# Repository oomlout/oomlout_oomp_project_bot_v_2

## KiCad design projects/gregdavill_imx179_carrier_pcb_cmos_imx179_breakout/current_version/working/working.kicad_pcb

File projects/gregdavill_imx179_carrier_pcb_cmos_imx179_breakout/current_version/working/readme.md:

# imx179_carrier_pcb
 
## summary 
* id: gregdavill_imx179_carrier_pcb_cmos_imx179_breakout
* user: gregdavill
* name: imx179_carrier_pcb
* board: cmos_imx179_breakout
* repo: https://github.com/gregdavill/imx179-carrier-pcb
* src_file_repo_kicad_pcb: hardware/cmos-imx179/cmos-imx179-breakout.kicad_pcb
* src_file_repo_kicad_pcb_link: https://github.com/gregdavill/imx179-carrier-pcb/tree/master/hardware/cmos-imx179/cmos-imx179-breakout.kicad_pcb

* src_file_repo_sch: hardware/cmos-imx179/cmos-imx179-breakout.sch
* src_file_repo_sch_link: https://github.com/gregdavill/imx179-carrier-pcb/tree/master/hardware/cmos-imx179/cmos-imx179-breakout.sch
* full details link: https://github.com/oomlout/oomlout_oomp_project_bot_v_2/tree/main/projects/gregdavill_imx179_carrier_pcb_cmos_imx179_breakout/current_version/working

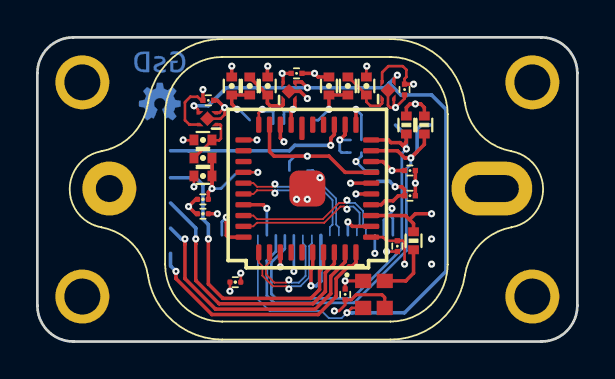
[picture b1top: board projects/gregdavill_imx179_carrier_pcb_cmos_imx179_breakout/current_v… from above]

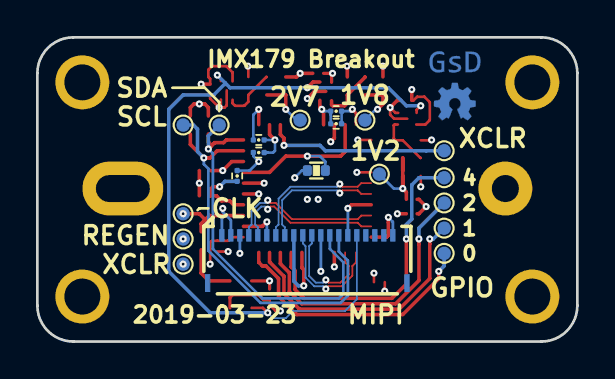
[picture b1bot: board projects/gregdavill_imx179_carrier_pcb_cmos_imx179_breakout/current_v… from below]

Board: 4 copper layers, 30.0 x 16.9 mm, 34 parts (7 on the bottom side), 20 nets.

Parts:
C1, C3, C5, C9, C10, C11: 1uF; C_0402
C7, C12, C13, C14, C15, C16, C17, C18, C19, C20, C21, C22, C23, C24, C25: 100nF; C_0201
J1: Conn_01x20; 5034802000
L1, L2, L3: 600R; C_0402
R1, R2: 2.2K; R_0402
R3: 22R; R_0402
R4: 0R; R_0402
U1: NCP114-120; X2SON_4_1.0x1.0mm
U2: NCP167-180; X2SON_4_1.0x1.0mm
U3: imx179-plcc40; PLCC-40_sony
U4: NCP167-270; X2SON_4_1.0x1.0mm
U5: 24.00 MHz; CDFN3225-4LD-PL-1

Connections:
+1V2: C5.1, C7.1, C18.1, C22.1, C23.1, C24.1, C25.1, L1.1, U3.5, U3.26, U3.37
+1V8: C10.1, C12.1, C13.1, C19.1, C20.1, C21.1, L2.1, R1.1, R2.1, U3.29, U5.1
+2V7: C11.1, C14.1, L3.1, U3.3, U3.33
+3V3: C15.1, C16.1, C17.1, J1.1, J1.2, U1.4, U2.4, U4.4
/AGND: R4.1, U3.4, U3.32
/CAM_SCL: J1.14, R1.2, U3.34
/CAM_SDA: J1.13, R2.2, U3.35
/CLK_IN: R3.2, U3.28
/CLK_N: J1.5, U3.14
/CLK_P: J1.4, U3.13
/DATA0_N: J1.8, U3.11
/DATA0_P: J1.7, U3.10
/DATA1_N: J1.11, U3.17
/DATA1_P: J1.10, U3.16
/ENABLE: J1.16, U1.3, U2.3, U4.3, U5.2
GND: C1.2, C3.2, C5.2, C7.2, C9.2, C10.2, C11.2, C12.2, C13.2, C14.2, C15.2, C16.2, C17.2, C18.2, C19.2, C20.2, C21.2, C22.2, C23.2, C24.2, C25.2, J1.3, J1.6, J1.9, J1.12, J1.15, J1.20, R4.2, U1.2, U2.2, U3.2, U3.6, U3.9, U3.12, U3.15, U3.18, U3.21, U3.27, U3.36, U3.41, U4.2, U5.3
unnamed: C1.1, L2.2, U2.1
unnamed: C3.1, L1.2, U1.1
unnamed: C9.1, L3.2, U4.1
unnamed: R3.1, U5.4

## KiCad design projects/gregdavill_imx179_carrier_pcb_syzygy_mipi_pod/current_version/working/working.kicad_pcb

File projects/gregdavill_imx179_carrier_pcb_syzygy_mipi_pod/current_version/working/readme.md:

# imx179_carrier_pcb
 
## summary 
* id: gregdavill_imx179_carrier_pcb_syzygy_mipi_pod
* user: gregdavill
* name: imx179_carrier_pcb
* board: syzygy_mipi_pod
* repo: https://github.com/gregdavill/imx179-carrier-pcb
* src_file_repo_kicad_pcb: hardware/syzygy-mipi-pod/syzygy-mipi-pod.kicad_pcb
* src_file_repo_kicad_pcb_link: https://github.com/gregdavill/imx179-carrier-pcb/tree/master/hardware/syzygy-mipi-pod/syzygy-mipi-pod.kicad_pcb

* src_file_repo_sch: hardware/cmos-imx179/cmos-imx179-breakout.sch
* src_file_repo_sch_link: https://github.com/gregdavill/imx179-carrier-pcb/tree/master/hardware/cmos-imx179/cmos-imx179-breakout.sch
* full details link: https://github.com/oomlout/oomlout_oomp_project_bot_v_2/tree/main/projects/gregdavill_imx179_carrier_pcb_syzygy_mipi_pod/current_version/working

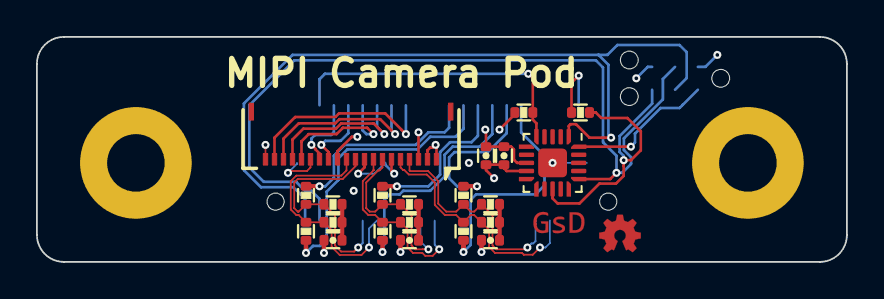
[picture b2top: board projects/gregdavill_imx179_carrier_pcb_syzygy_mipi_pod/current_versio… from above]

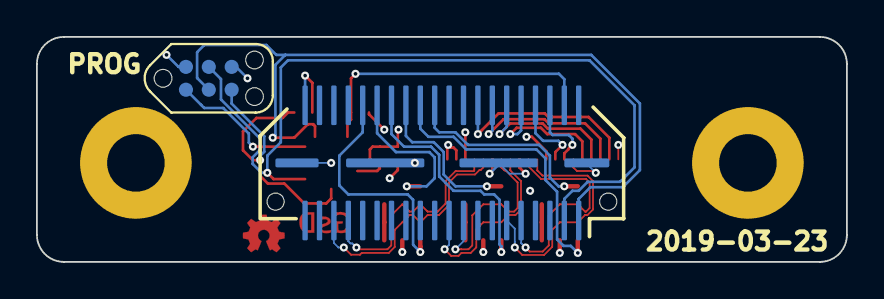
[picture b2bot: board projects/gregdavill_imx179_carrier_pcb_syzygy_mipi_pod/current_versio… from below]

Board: 4 copper layers, 45.0 x 12.5 mm, 23 parts (2 on the bottom side), 28 nets.

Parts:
C1, C2, C3: 100pF; C_0402
C14: 100nF; C_0402
C15: 1uF; C_0402
J1: SYZYGY-STD; SYZYGY_standard_pod
J2: Conn_01x20; 5034802000
J3: TagConnect; TC2030-NL_SMALL
R1, R14: 10K; R_0402
R2, R3, R4, R5, R6, R7: 150R; R_0402
R8, R9, R10, R11, R12, R13: 100R; R_0402
U1: ATtiny44A-MMH; QFN-20-1EP_3x3mm_P0.45mm_EP1.6x1.6mm

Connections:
+3V3: C14.1, C15.1, J1.40, J2.1, J2.2, J3.2, R1.1, R14.1, U1.9
/CAM0_CLK_N: J1.35, J2.5, R3.1, R9.2
/CAM0_CLK_P: J1.33, J2.4, R2.2, R8.2
/CAM0_D0_N: J1.19, J2.8, R5.1, R11.2
/CAM0_D0_P: J1.17, J2.7, R4.2, R10.2
/CAM0_D1_N: J1.11, J2.11, R7.1, R13.2
/CAM0_D1_P: J1.9, J2.10, R6.2, R12.2
/CAM0_SCL: J1.6, J2.14
/CAM0_SDA: J1.8, J2.13
/GPIO0: J1.10, J2.16
/GPIO1: J1.12, J2.17
/GPIO2: J1.14, J2.18
/GPIO3: J1.16, J2.19
/Peripheral MCU/MISO: J3.1, U1.20
/Peripheral MCU/~RESET: J3.5, R14.2, U1.13
/RGA: J1.4, R1.2, U1.5
/SCL: J1.1, J3.3, U1.1
/SDA: J1.3, J3.4, U1.16
/TERM_0_N: J1.28, R11.1
/TERM_0_P: J1.26, R10.1
/TERM_1_N: J1.24, R13.1
/TERM_1_P: J1.22, R12.1
/TERM_CLK_N: J1.32, R9.1
/TERM_CLK_P: J1.30, R8.1
GND: C1.2, C2.2, C3.2, C14.2, C15.2, J1.41, J2.3, J2.6, J2.9, J2.12, J2.15, J2.20, J3.6, U1.8, U1.21
unnamed: C1.1, R2.1, R3.2
unnamed: C2.1, R4.1, R5.2
unnamed: C3.1, R6.1, R7.2

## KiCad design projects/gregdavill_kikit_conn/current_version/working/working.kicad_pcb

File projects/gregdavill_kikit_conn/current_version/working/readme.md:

# kikit
 
## summary 
* id: gregdavill_kikit_conn
* user: gregdavill
* name: kikit
* board: conn
* repo: https://github.com/gregdavill/KiKit
* src_file_repo_kicad_pcb: test/resources/conn-fail.kicad_pcb
* src_file_repo_kicad_pcb_link: https://github.com/gregdavill/KiKit/tree/master/test/resources/conn-fail.kicad_pcb

* src_file_repo_sch: 
* src_file_repo_sch_link: https://github.com/gregdavill/KiKit/tree/master/
* full details link: https://github.com/oomlout/oomlout_oomp_project_bot_v_2/tree/main/projects/gregdavill_kikit_conn/current_version/working

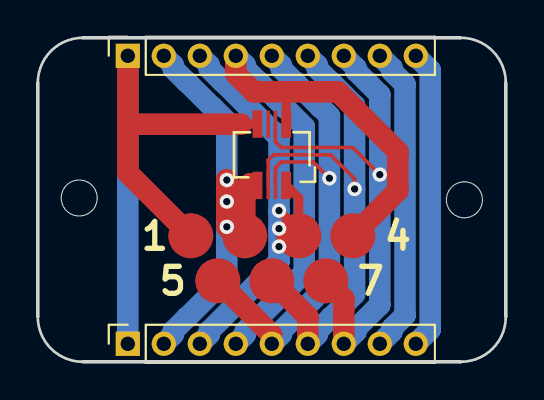
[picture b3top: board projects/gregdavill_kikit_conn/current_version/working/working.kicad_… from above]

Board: 2 copper layers, 26.0 x 18.0 mm, 6 parts (0 on the bottom side), 9 nets.

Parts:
H1, H2: MountingHole; MountingHole_2mm
J1: IN; PinSocket_1x09_P2.00mm_Vertical
J2: OUT; PinSocket_1x09_P2.00mm_Vertical
J3: POGO; pogo_pads_4_3
J4: Molex; molex-505004-0812

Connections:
1: J1.1, J2.1, J3.1, J4.8
2: J1.2, J2.2, J3.2, J4.7
3: J1.3, J2.3, J3.3, J4.1
4: J1.4, J2.4, J3.4, J4.2
5: J1.5, J2.5, J3.5, J4.3
6: J1.6, J2.6, J3.6, J4.5
7: J1.7, J2.7, J3.7, J4.4
8: J1.8, J2.8
9: J1.9, J2.9

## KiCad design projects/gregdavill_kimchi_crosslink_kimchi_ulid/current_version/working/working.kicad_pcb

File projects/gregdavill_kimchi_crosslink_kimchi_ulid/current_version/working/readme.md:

# kimchi_crosslink
 
## summary 
* id: gregdavill_kimchi_crosslink_kimchi_ulid
* user: gregdavill
* name: kimchi_crosslink
* board: kimchi_ulid
* repo: https://github.com/gregdavill/kimchi-crosslink
* src_file_repo_kicad_pcb: kimchi_ulid.kicad_pcb
* src_file_repo_kicad_pcb_link: https://github.com/gregdavill/kimchi-crosslink/tree/main/kimchi_ulid.kicad_pcb
* src_file_repo_kicad_sch: kimchi_ulid.kicad_sch
* src_file_repo_kicad_sch_link: https://github.com/gregdavill/kimchi-crosslink/tree/main/kimchi_ulid.kicad_sch

* src_file_repo_sch: kimchi_ulid.sch
* src_file_repo_sch_link: https://github.com/gregdavill/kimchi-crosslink/tree/main/kimchi_ulid.sch
* full details link: https://github.com/oomlout/oomlout_oomp_project_bot_v_2/tree/main/projects/gregdavill_kimchi_crosslink_kimchi_ulid/current_version/working

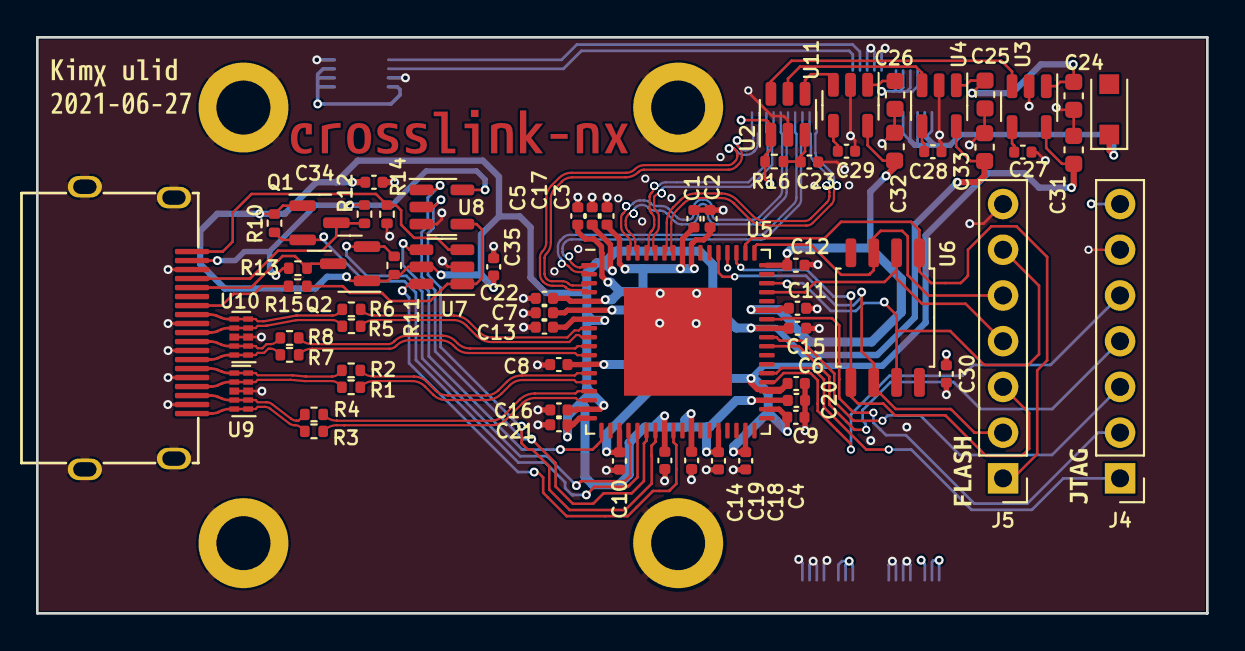
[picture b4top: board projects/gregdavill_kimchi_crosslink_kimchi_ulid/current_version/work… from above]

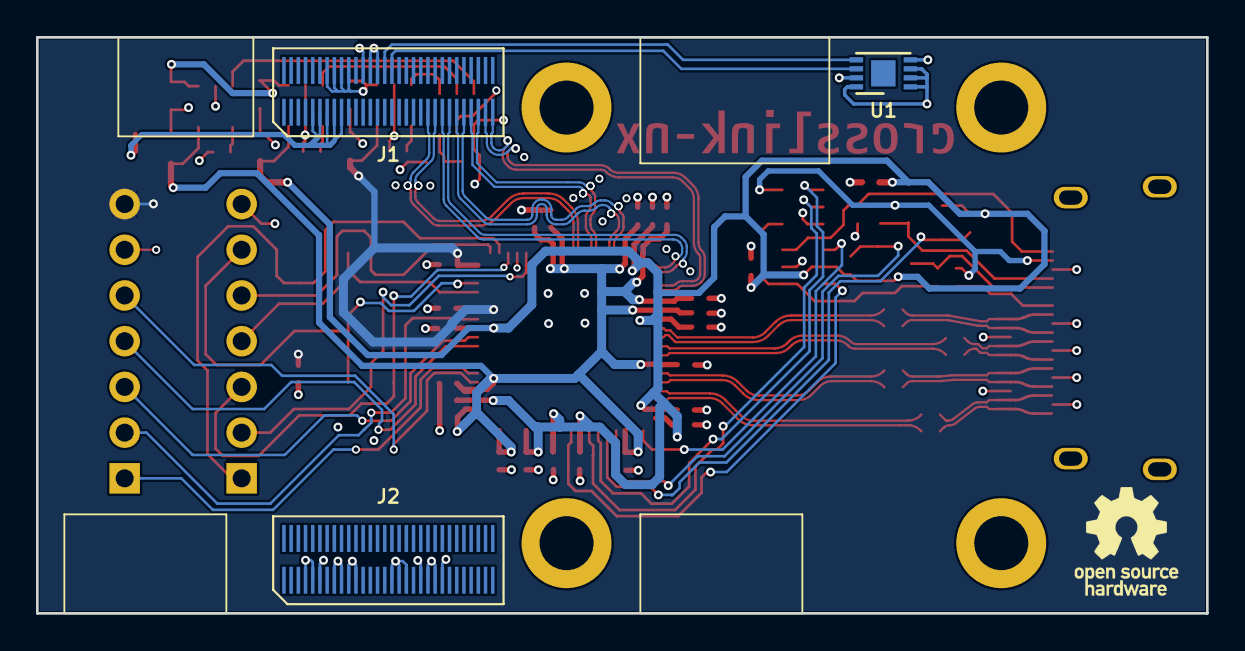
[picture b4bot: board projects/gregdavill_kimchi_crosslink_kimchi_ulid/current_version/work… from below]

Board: 4 copper layers, 65.0 x 32.0 mm, 80 parts (9 on the bottom side), 66 nets.

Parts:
C1, C2, C3, C4, C5, C6, C7, C8, C9, C10, C11, C12, C13, C14, C15, C16, C17, C18, C19, C20, C21, C22, C30, C34, C35: 0.1uF; C_0402_1005Metric
C23: C; C_0402_1005Metric
C24, C25, C26: 4.7uF; C_0603_1608Metric
C27, C28, C29: 0.01uF; C_0402_1005Metric
C31, C32, C33: 10uF; C_0603_1608Metric
D1: PMEG1020EH; D_SOD-123F
H1, H2, H3, H4: MountingHole_Pad; MountingHole_M2_Standoff
J1, J2: DF40HC(3.5)-60DS
J3: HDMI_A_1.4; HDMI-10029449-111RLF
J4: Jtag; PinHeader_1x07_P2.54mm_Vertical
J5: Flash; PinHeader_1x07_P2.54mm_Vertical
K1: KIMCHI_MICRO
LOGO1: Logo_Open_Hardware_Small; OSHW-Logo_5.7x6mm_SilkScreen
Q1, Q2: 2N7002; SOT-23
R1, R2, R3, R4, R5, R6, R7, R8, R16: R; R_0402_1005Metric
R10, R11, R12, R13: 2k2; R_0402_1005Metric
R14: 47k; R_0402_1005Metric
R15: 100R; R_0402_1005Metric
U1: 24C32; DFN-8-1EP_3x2mm_P0.5mm_EP1.36x1.46mm
U2: LM3880; SOT-23-6
U3, U4, U11: LD3985M27R_SOT23; SOT-23-5
U5: LIFCL40-NX; QFN-72-1EP_10x10mm_P0.5mm_EP6x6mm
U6: W25Q32JVSS; SOIC-8_5.23x5.23mm_P1.27mm
U7: 74LVC2G17; SOT-23-6
U8: 74LVC1G125; SOT-23-5
U9, U10: TPD4E02B04DQA; USON-10_2.5x1.0mm_P0.5mm
svg2mod, svg2mod#2, svg2mod#3, svg2mod#4, svg2mod#5: G***; svg2mod

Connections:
+1V0: C1.1, C2.1, C3.1, C4.1, C5.1, C6.1, C7.1, C8.1, C9.1, C10.1, C22.1, C31.1, U3.5 (VOUT), U5.5 (VCC), U5.6 (VCC), U5.12 (VCCPLL_LLC), U5.21 (VCC), U5.35 (VCC), U5.38 (VCCPLL_LRC), U5.40 (VCC), U5.62 (VCC), U5.63 (VCCPLLDPHY0), U5.70 (VCCDPHY0), U5.72 (VCCDPHY0)
+1V8: C13.1, C14.1, C15.1, C16.1, C17.1, C18.1, C19.1, C20.1, C21.1, C33.1, C34.1, C35.1, Q1.1 (G), Q2.1 (G), R10.2, R11.2, U4.5 (VOUT), U5.7 (VCCAUX), U5.17 (VCCAUXH5), U5.18 (VCCIO5), U5.26 (VCCIO3), U5.29 (VCCAUXH3), U5.32 (VCCIO3), U5.39 (VCCADC18), U5.47 (VCCAUX), U5.71 (VCCADPHY0), U7.5 (VCC)
+3V3: C11.1, C12.1, C30.1, C32.1, J4.7, U5.49 (VCCIO1), U5.54 (VCCIO0), U11.5 (VOUT)
/DISP_CK_N: J1.35, U5.69 (DPHY0_CKN)
/DISP_CK_P: J1.36, U5.68 (DPHY0_CKP)
/DISP_D0_N: J1.31, U5.3 (DPHY0_DN0)
/DISP_D0_P: J1.32, U5.4 (DPHY0_DP0)
/DISP_D1_N: J1.33, U5.67 (DPHY0_DN1)
/DISP_D1_P: J1.34, U5.66 (DPHY0_DP1)
/DISP_D2_N: J1.37, U5.2 (DPHY0_DN2)
/DISP_D2_P: J1.38, U5.1 (DPHY0_DP2)
/DISP_D3_N: J1.39, U5.65 (DPHY0_DN3)
/DISP_D3_P: J1.40, U5.64 (DPHY0_DP3)
/FLASH_CS: J5.1, U5.56 (PT78A/MCSN/PCLKT0_1), U6.1 (~CS)
/FLASH_MISO|IO1: J5.4, U5.51 (PT80A/MISO/MD1), U6.2 (DO(IO1))
/FLASH_MOSI|IO0: J5.3, U5.57 (PT78B/MOSI/MD0), U6.5 (DI(IO0))
/FLASH_~HLD|~RST|IO3: J5.6, U5.52 (PT82A/MD3), U6.7 (IO3)
/FLASH_~WP|IO2: J5.5, U5.55 (PT80B/MD2), U6.3 (IO2)
/IO: J4.1, U5.42 (PR11A/SDA/USER_SDA)
/TCK: J4.5, U5.41 (PR13A/TCK/SCLK/PMU_EXT_CLK)
/TDI: J4.3, U5.46 (PR8B/TDI/SSI)
/TDO: J4.4, U5.45 (PR10B/TDO/SSO)
/TMS: J4.2, U5.48 (PR6B/TMS/SCSN)
/_tmds_clk+: J3.10 (CK+), R5.2, U10.4 (IO3)
/_tmds_clk-: J3.12 (CK-), R6.2, U10.5 (IO4)
/_tmds_d0+: J3.7 (D0+), R7.2, U10.1 (IO1)
/_tmds_d0-: J3.9 (D0-), R8.2, U10.2 (IO2)
/_tmds_d1+: J3.4 (D1+), R1.2, U9.4 (IO3)
/_tmds_d1-: J3.6 (D1-), R2.2, U9.5 (IO4)
/_tmds_d2+: J3.1 (D2+), R3.2, U9.1 (IO1)
/_tmds_d2-: J3.3 (D2-), R4.2, U9.2 (IO2)
/en0: U2.6 (FLAG1), U3.3 (INH)
/en1: U2.5 (FLAG2), U4.3 (INH)
/en2: U2.4 (FLAG3), U11.3 (INH)
/iCE_SCK: J5.2, U5.59 (PT76A/MCLK/PCLKT0_0), U6.6 (CLK)
/tmds_clk+: R5.1, U5.9 (PB12A/PCLKT5_3)
/tmds_clk-: R6.1, U5.8 (PB12B/PCLKC5_3/VREF5_2)
/tmds_d0+: R7.1, U5.11 (PB8A/PCLKT5_1/LLC_GPLL0T_IN/ADC_CP3)
/tmds_d0-: R8.1, U5.10 (PB8B/PCLKC5_1/LLC_GPLL0C_IN/ADC_CN3)
/tmds_d1+: R1.1, U5.14 (PB4A/CDR_RXP0/VREF5_1/ADC_CP0/COMP1P)
/tmds_d1-: R2.1, U5.13 (PB4B/CDR_RXN0/ADC_CN0/COMP1N)
/tmds_d2+: R3.1, U5.16 (PB6A/PCLKT5_0/CDR_RXP1/ADC_CP1/COMP2P)
/tmds_d2-: R4.1, U5.15 (PB6B/PCLKC5_0/CDR_RXN1/ADC_CN1/COMP2N)
GND: C1.2, C2.2, C3.2, C4.2, C5.2, C6.2, C7.2, C8.2, C9.2, C10.2, C11.2, C12.2, C13.2, C14.2, C15.2, C16.2, C17.2, C18.2, C19.2, C20.2, C21.2, C22.2, C23.2, C24.2, C25.2, C26.2, C27.2, C28.2, C29.2, C30.2, C31.2, C32.2, C33.2, C34.2, C35.2, H1.1, H2.1, H3.1, H4.1, J1.12, J1.13, J1.14, J2.38, J2.39, J2.40, J2.41, J2.50, J2.51, J2.52, J2.53, J3.2 (D2S), J3.5 (D1S), J3.8 (D0S), J3.11 (CKS), J3.17 (GND), J3.SH, J4.6, J5.7, R14.1, U1.4 (GND), U1.7 (WP), U2.2 (GND), U3.2 (GND), U4.2 (GND), U5.73 (GND), U7.2 (GND), U8.3 (GND), U9.3 (G), U9.8 (G), U10.3 (G), U10.8 (G), U11.2 (GND)
I2C4_SCL: J1.16, U1.6 (SCL)
I2C4_SDA: J1.15, U1.5 (SDA)
unnamed: C23.1, R16.2, U2.3 (EN)
unnamed: C27.1, U3.4 (BYP)
unnamed: C28.1, U4.4 (BYP)
unnamed: C29.1, U11.4 (BYP)
unnamed: J3.13 (CEC), R15.1
unnamed: J3.15 (SCL), Q2.3 (D), R13.1
unnamed: J3.16 (SDA), Q1.3 (D), R12.1
unnamed: J3.19 (HPD/HEAC-), R14.2, U7.3
unnamed: Q1.2 (S), R10.1, U5.23 (PB54B/PCLKC3_0/ADC_CN5)
unnamed: Q2.2 (S), R11.1, U5.22 (PB54A/PCLKT3_0/VREF3_1/ADC_CP5)
unnamed: R15.2, U7.1, U8.4
unnamed: U5.19 (PB10A/PCLKT5_2/ADC_CP2/COMP3P), U7.4
unnamed: U5.24 (PB58A/PCLKT3_1/ADC_CP6), U8.1
unnamed: U5.25 (PB58B/PCLKC3_1/ADC_CN6), U8.2
unnamed: U5.27 (PB68A/ADC_CP8), U7.6
VCHG: D1.1 (K), J1.52, J1.53, J1.54, J1.55, J1.56
VDD: J3.18 (+5V), R12.2, R13.2, U8.5 (VDD)
VDD_1V8: J2.43, J2.44, J2.45
VDD_3V3: C24.1, C25.1, J2.55, J2.56, J2.57, R16.1, U1.1 (A0), U1.2 (A1), U1.3 (A2), U1.8 (VCC), U2.1 (VCC), U3.1 (VIN), U4.1 (VIN)
VDD_5V: C26.1, J1.7, J1.8, J1.9, J1.10, U11.1 (VIN)

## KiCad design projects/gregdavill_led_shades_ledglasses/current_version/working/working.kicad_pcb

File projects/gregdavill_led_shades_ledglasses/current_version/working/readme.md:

# led_shades
 
## summary 
* id: gregdavill_led_shades_ledglasses
* user: gregdavill
* name: led_shades
* board: ledglasses
* repo: https://github.com/gregdavill/led-shades
* src_file_repo_kicad_pcb: hw/ledGlasses.kicad_pcb
* src_file_repo_kicad_pcb_link: https://github.com/gregdavill/led-shades/tree/master/hw/ledGlasses.kicad_pcb

* src_file_repo_sch: hw/ledGlasses.sch
* src_file_repo_sch_link: https://github.com/gregdavill/led-shades/tree/master/hw/ledGlasses.sch
* full details link: https://github.com/oomlout/oomlout_oomp_project_bot_v_2/tree/main/projects/gregdavill_led_shades_ledglasses/current_version/working

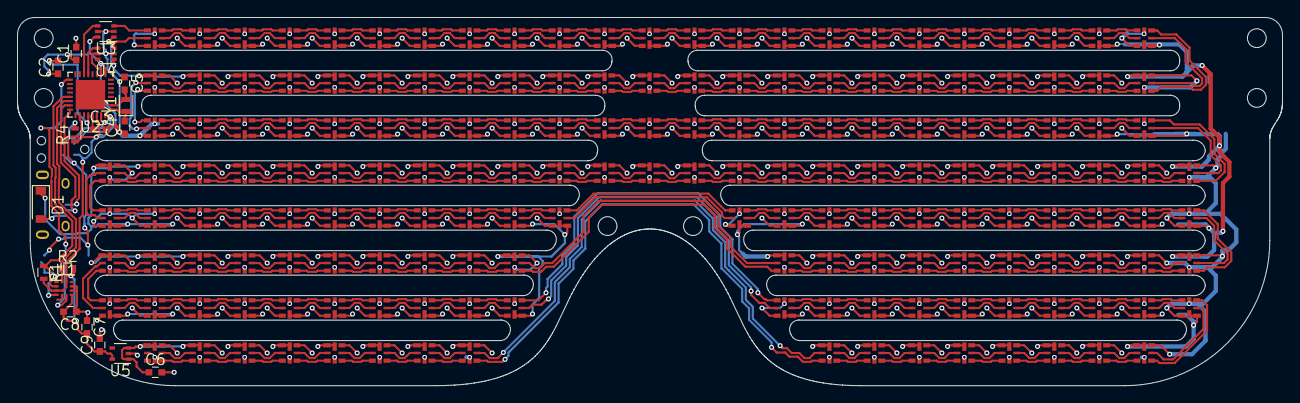
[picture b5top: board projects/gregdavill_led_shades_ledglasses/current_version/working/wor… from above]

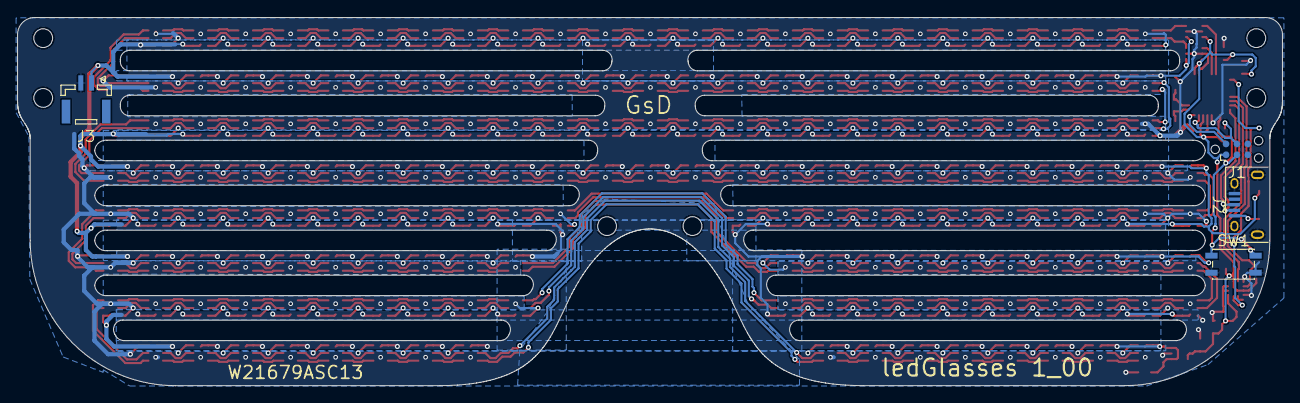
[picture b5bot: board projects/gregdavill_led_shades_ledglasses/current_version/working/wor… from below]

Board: 2 copper layers, 148.1 x 43.1 mm, 201 parts (4 on the bottom side), 361 nets.

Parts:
C1, C2, C7, C8: 100nF; C_0603
C3, C6, C9: 1uF; C_0603
C4, C5: 16pF; C_0603
D1: Diode; D_SOD-123
J1: TC2030-CTX; Tag-Connect_TC2030-IDC-NL
J2: USB_OTG; USB_Micro-B
J3: PWR IN; JST_GH_BM02B-GHS-TBT_02x1.25mm_Straight
LED1, LED2, LED3, LED4, LED5, LED6, LED7, LED8, LED9, LED10, LED11, LED12, LED13, LED14, LED15, LED16, LED17, LED18, LED19, LED20, LED21, LED22, LED23, LED24, LED25, LED26, LED27, LED28, LED29, LED30, LED31, LED32, LED33, LED34, LED35, LED36, LED37, LED38, LED39, LED40, LED41, LED42, LED43, LED44, LED45, LED46, LED47, LED48, LED49, LED50, LED51, LED52, LED53, LED54, LED55, LED56, LED57, LED58, LED59, LED60, LED61, LED62, LED63, LED64, LED65, LED66, LED67, LED68, LED69, LED70, LED71, LED72, LED73, LED74, LED75, LED76, LED77, LED78, LED79, LED80, LED81, LED82, LED83, LED84, LED85, LED86, LED87, LED88, LED89, LED90, LED91, LED92, LED93, LED94, LED95, LED96, LED97, LED98, LED99, LED100, LED101, LED102, LED103, LED104, LED105, LED106, LED107, LED108, LED109, LED110, LED111, LED112, LED113, LED114, LED115, LED116, LED117, LED118, LED119, LED120, LED121, LED122, LED123, LED124, LED125, LED126, LED127, LED128, LED129, LED130, LED131, LED132, LED133, LED134, LED135, LED136, LED137, LED138, LED139, LED140, LED141, LED142, LED143, LED144, LED145, LED146, LED147, LED148, LED149, LED150, LED151, LED152, LED153, LED154, LED155, LED156, LED157, LED158, LED159, LED160, LED161, LED162, LED163, LED164, LED165, LED166, LED167, LED168, LED169, LED170, LED171, LED172: APA102; APA102_2020
MH1, MH2, MH3, MH4, MH5, MH6: MountingHole; MountingHole_2.2mm_M2_DIN965
R1, R2: 4K7; R_0603
R4: 1K; R_0603
SW1: TACT_SWITCH; SW_SPST_EVQP2
U1: BMA255
U2: SAMD20E17A-MU; QFN-32-1EP_5x5mm_Pitch0.5mm
U3, U4: SN74LVC1T45; SOT-363_SC-70-6
U5: MIC5365; SOT-353_SC-70-5
Y1: 32.768kHz; Crystal_SMD_2012-2pin_2.0x1.2mm

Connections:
+3V3: C1.1, C2.1, C7.2, C8.2, C9.1, J1.1, R1.2, R2.2, R4.1, U1.3, U1.7, U1.11, U2.9, U2.30, U3.6, U4.6, U5.5
+5V: C6.1, D1.1, J3.1, LED1.1, LED1.7, LED2.1, LED2.7, LED3.1, LED3.7, LED4.1, LED4.7, LED5.1, LED5.7, LED6.1, LED6.7, LED7.1, LED7.7, LED8.1, LED8.7, LED9.1, LED9.7, LED10.1, LED10.7, LED11.1, LED11.7, LED12.1, LED12.7, LED13.1, LED13.7, LED14.1, LED14.7, LED15.1, LED15.7, LED16.1, LED16.7, LED17.1, LED17.7, LED18.1, LED18.7, LED19.1, LED19.7, LED20.1, LED20.7, LED21.1, LED21.7, LED22.1, LED22.7, LED23.1, LED23.7, LED24.1, LED24.7, LED25.1, LED25.7, LED26.1, LED26.7, LED27.1, LED27.7, LED28.1, LED28.7, LED29.1, LED29.7, LED30.1, LED30.7, LED31.1, LED31.7, LED32.1, LED32.7, LED33.1, LED33.7, LED34.1, LED34.7, LED35.1, LED35.7, LED36.1, LED36.7, LED37.1, LED37.7, LED38.1, LED38.7, LED39.1, LED39.7, LED40.1, LED40.7, LED41.1, LED41.7, LED42.1, LED42.7, LED43.1, LED43.7, LED44.1, LED44.7, LED45.1, LED45.7, LED46.1, LED46.7, LED47.1, LED47.7, LED48.1, LED48.7, LED49.1, LED49.7, LED50.1, LED50.7, LED51.1, LED51.7, LED52.1, LED52.7, LED53.1, LED53.7, LED54.1, LED54.7, LED55.1, LED55.7, LED56.1, LED56.7, LED57.1, LED57.7, LED58.1, LED58.7, LED59.1, LED59.7, LED60.1, LED60.7, LED61.1, LED61.7, LED62.1, LED62.7, LED63.1, LED63.7, LED64.1, LED64.7, LED65.1, LED65.7, LED66.1, LED66.7, LED67.1, LED67.7, LED68.1, LED68.7, LED69.1, LED69.7, LED70.1, LED70.7, LED71.1, LED71.7, LED72.1, LED72.7, LED73.1, LED73.7, LED74.1, LED74.7, LED75.1, LED75.7, LED76.1, LED76.7, LED77.1, LED77.7, LED78.1, LED78.7, LED79.1, LED79.7, LED80.1, LED80.7, LED81.1, LED81.7, LED82.1, LED82.7, LED83.1, LED83.7, LED84.1, LED84.7, LED85.1, LED85.7, LED86.1, LED86.7, LED87.1, LED87.7, LED88.1, LED88.7, LED89.1, LED89.7, LED90.1, LED90.7, LED91.1, LED91.7, LED92.1, LED92.7, LED93.1, LED93.7, LED94.1, LED94.7, LED95.1, LED95.7, LED96.1, LED96.7, LED97.1, LED97.7, LED98.1, LED98.7, LED99.1, LED99.7, LED100.1, LED100.7, LED101.1, LED101.7, LED102.1, LED102.7, LED103.1, LED103.7, LED104.1, LED104.7, LED105.1, LED105.7, LED106.1, LED106.7, LED107.1, LED107.7, LED108.1, LED108.7, LED109.1, LED109.7, LED110.1, LED110.7, LED111.1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
/clk20: LED20.2, LED21.5
/clk40: LED40.2, LED41.5
/clk60: LED60.2, LED61.5
/clk80: LED80.2, LED81.5
/clk104: LED104.2, LED105.5
/clk128: LED128.2, LED129.5
/clk152: LED152.2, LED153.5
/dat20: LED20.3, LED21.4
/dat40: LED40.3, LED41.4
/dat60: LED60.3, LED61.4
/dat80: LED80.3, LED81.4
/dat104: LED104.3, LED105.4
/dat128: LED128.3, LED129.4
/dat152: LED152.3, LED153.4
ACC_INT2: U1.6, U2.17
ACC_SCL: R2.1, U1.12, U2.22
ACC_SDA: R1.1, U1.2, U2.21
APA_CLK: U2.13, U4.4
APA_DAT: U2.14, U3.4
GND: C1.2, C2.2, C3.2, C4.1, C5.1, C6.2, C7.1, C8.1, C9.2, J1.5, J2.5, J2.6, J3.2, LED1.6, LED1.8, LED2.6, LED2.8, LED3.6, LED3.8, LED4.6, LED4.8, LED5.6, LED5.8, LED6.6, LED6.8, LED7.6, LED7.8, LED8.6, LED8.8, LED9.6, LED9.8, LED10.6, LED10.8, LED11.6, LED11.8, LED12.6, LED12.8, LED13.6, LED13.8, LED14.6, LED14.8, LED15.6, LED15.8, LED16.6, LED16.8, LED17.6, LED17.8, LED18.6, LED18.8, LED19.6, LED19.8, LED20.6, LED20.8, LED21.6, LED21.8, LED22.6, LED22.8, LED23.6, LED23.8, LED24.6, LED24.8, LED25.6, LED25.8, LED26.6, LED26.8, LED27.6, LED27.8, LED28.6, LED28.8, LED29.6, LED29.8, LED30.6, LED30.8, LED31.6, LED31.8, LED32.6, LED32.8, LED33.6, LED33.8, LED34.6, LED34.8, LED35.6, LED35.8, LED36.6, LED36.8, LED37.6, LED37.8, LED38.6, LED38.8, LED39.6, LED39.8, LED40.6, LED40.8, LED41.6, LED41.8, LED42.6, LED42.8, LED43.6, LED43.8, LED44.6, LED44.8, LED45.6, LED45.8, LED46.6, LED46.8, LED47.6, LED47.8, LED48.6, LED48.8, LED49.6, LED49.8, LED50.6, LED50.8, LED51.6, LED51.8, LED52.6, LED52.8, LED53.6, LED53.8, LED54.6, LED54.8, LED55.6, LED55.8, LED56.6, LED56.8, LED57.6, LED57.8, LED58.6, LED58.8, LED59.6, LED59.8, LED60.6, LED60.8, LED61.6, LED61.8, LED62.6, LED62.8, LED63.6, LED63.8, LED64.6, LED64.8, LED65.6, LED65.8, LED66.6, LED66.8, LED67.6, LED67.8, LED68.6, LED68.8, LED69.6, LED69.8, LED70.6, LED70.8, LED71.6, LED71.8, LED72.6, LED72.8, LED73.6, LED73.8, LED74.6, LED74.8, LED75.6, LED75.8, LED76.6, LED76.8, LED77.6, LED77.8, LED78.6, LED78.8, LED79.6, LED79.8, LED80.6, LED80.8, LED81.6, LED81.8, LED82.6, LED82.8, LED83.6, LED83.8, LED84.6, LED84.8, LED85.6, LED85.8, LED86.6, LED86.8, LED87.6, LED87.8, LED88.6, LED88.8, LED89.6, LED89.8, LED90.6, LED90.8, LED91.6, LED91.8, LED92.6, LED92.8, LED93.6, LED93.8, LED94.6, LED94.8, LED95.6, LED95.8, LED96.6, LED96.8, LED97.6, LED97.8, LED98.6, LED98.8, LED99.6, LED99.8, LED100.6, LED100.8, LED101.6, LED101.8, LED102.6, LED102.8, LED103.6, LED103.8, LED104.6, LED104.8, LED105.6, LED105.8, LED106.6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
unnamed: C3.1, U2.29
unnamed: C4.2, U2.1, Y1.1
unnamed: C5.2, U2.2, Y1.2
unnamed: D1.2, J2.1
unnamed: LED1.2, LED2.5
unnamed: LED1.3, LED2.4
unnamed: LED1.4, U3.3
unnamed: LED1.5, U4.3
unnamed: LED2.2, LED3.5
unnamed: LED2.3, LED3.4
unnamed: LED3.2, LED4.5
unnamed: LED3.3, LED4.4
unnamed: LED4.2, LED5.5
unnamed: LED4.3, LED5.4
unnamed: LED5.2, LED6.5
unnamed: LED5.3, LED6.4
unnamed: LED6.2, LED7.5
unnamed: LED6.3, LED7.4
unnamed: LED7.2, LED8.5
unnamed: LED7.3, LED8.4
unnamed: LED8.2, LED9.5
unnamed: LED8.3, LED9.4
unnamed: LED10.2, LED11.5
unnamed: LED10.3, LED11.4
unnamed: LED9.3, LED10.4
unnamed: LED9.2, LED10.5
unnamed: LED11.2, LED12.5
unnamed: LED11.3, LED12.4
unnamed: LED12.2, LED13.5
unnamed: LED12.3, LED13.4
unnamed: LED13.2, LED14.5
unnamed: LED13.3, LED14.4
unnamed: LED14.2, LED15.5
unnamed: LED14.3, LED15.4
unnamed: LED15.2, LED16.5
unnamed: LED15.3, LED16.4
unnamed: LED16.2, LED17.5
unnamed: LED16.3, LED17.4
unnamed: LED17.2, LED18.5
unnamed: LED17.3, LED18.4
unnamed: LED18.2, LED19.5
unnamed: LED18.3, LED19.4
unnamed: LED19.2, LED20.5
unnamed: LED19.3, LED20.4
unnamed: LED21.2, LED22.5
unnamed: LED21.3, LED22.4
unnamed: LED22.2, LED23.5
unnamed: LED22.3, LED23.4
unnamed: LED23.2, LED24.5
unnamed: LED23.3, LED24.4
unnamed: LED24.2, LED25.5
unnamed: LED24.3, LED25.4
unnamed: LED25.2, LED26.5
unnamed: LED25.3, LED26.4
unnamed: LED26.2, LED27.5
unnamed: LED26.3, LED27.4
unnamed: LED27.2, LED28.5
unnamed: LED27.3, LED28.4
unnamed: LED28.2, LED29.5
unnamed: LED28.3, LED29.4
unnamed: LED29.2, LED30.5
unnamed: LED29.3, LED30.4
unnamed: LED30.2, LED31.5
unnamed: LED30.3, LED31.4
unnamed: LED31.2, LED32.5
unnamed: LED31.3, LED32.4
unnamed: LED32.2, LED33.5
unnamed: LED32.3, LED33.4
unnamed: LED33.2, LED34.5
unnamed: LED33.3, LED34.4
unnamed: LED34.2, LED35.5
unnamed: LED34.3, LED35.4
unnamed: LED35.2, LED36.5
unnamed: LED35.3, LED36.4
unnamed: LED36.2, LED37.5
unnamed: LED36.3, LED37.4
unnamed: LED37.2, LED38.5
unnamed: LED37.3, LED38.4
unnamed: LED38.2, LED39.5
unnamed: LED38.3, LED39.4
unnamed: LED39.2, LED40.5
unnamed: LED39.3, LED40.4
unnamed: LED41.2, LED42.5
unnamed: LED41.3, LED42.4
unnamed: LED42.2, LED43.5
unnamed: LED42.3, LED43.4
unnamed: LED43.2, LED44.5
unnamed: LED43.3, LED44.4
unnamed: LED44.2, LED45.5
unnamed: LED44.3, LED45.4
unnamed: LED45.2, LED46.5
unnamed: LED45.3, LED46.4
unnamed: LED46.2, LED47.5
unnamed: LED46.3, LED47.4
unnamed: LED47.2, LED48.5
unnamed: LED47.3, LED48.4
unnamed: LED48.2, LED49.5
unnamed: LED48.3, LED49.4
unnamed: LED49.2, LED50.5
unnamed: LED49.3, LED50.4
unnamed: LED50.2, LED51.5
unnamed: LED50.3, LED51.4
unnamed: LED51.2, LED52.5
unnamed: LED51.3, LED52.4
unnamed: LED52.2, LED53.5
unnamed: LED52.3, LED53.4
unnamed: LED53.2, LED54.5
unnamed: LED53.3, LED54.4
unnamed: LED54.2, LED55.5
unnamed: LED54.3, LED55.4
unnamed: LED55.2, LED56.5
unnamed: LED55.3, LED56.4
unnamed: LED56.2, LED57.5
unnamed: LED56.3, LED57.4
unnamed: LED57.2, LED58.5
unnamed: LED57.3, LED58.4
unnamed: LED58.2, LED59.5
unnamed: LED58.3, LED59.4
unnamed: LED59.2, LED60.5
unnamed: LED59.3, LED60.4
unnamed: LED61.2, LED62.5
unnamed: LED61.3, LED62.4
unnamed: LED62.2, LED63.5
unnamed: LED62.3, LED63.4
unnamed: LED63.2, LED64.5
unnamed: LED63.3, LED64.4
unnamed: LED64.2, LED65.5
unnamed: LED64.3, LED65.4
unnamed: LED65.2, LED66.5
unnamed: LED65.3, LED66.4
unnamed: LED66.2, LED67.5
unnamed: LED66.3, LED67.4
unnamed: LED67.2, LED68.5
unnamed: LED67.3, LED68.4
unnamed: LED68.2, LED69.5
unnamed: LED68.3, LED69.4
unnamed: LED69.2, LED70.5
unnamed: LED69.3, LED70.4
unnamed: LED70.2, LED71.5
unnamed: LED70.3, LED71.4
unnamed: LED71.2, LED72.5
unnamed: LED71.3, LED72.4
unnamed: LED72.2, LED73.5
unnamed: LED72.3, LED73.4
unnamed: LED73.2, LED74.5
unnamed: LED73.3, LED74.4
unnamed: LED74.2, LED75.5
unnamed: LED74.3, LED75.4
unnamed: LED75.2, LED76.5
unnamed: LED75.3, LED76.4
unnamed: LED76.2, LED77.5
unnamed: LED76.3, LED77.4
unnamed: LED77.2, LED78.5
unnamed: LED77.3, LED78.4
unnamed: LED78.2, LED79.5
unnamed: LED78.3, LED79.4
unnamed: LED79.2, LED80.5
unnamed: LED79.3, LED80.4
unnamed: LED81.2, LED82.5
unnamed: LED81.3, LED82.4
unnamed: LED82.2, LED83.5
unnamed: LED82.3, LED83.4
unnamed: LED83.2, LED84.5
unnamed: LED83.3, LED84.4
unnamed: LED84.2, LED85.5
unnamed: LED84.3, LED85.4
unnamed: LED85.2, LED86.5
unnamed: LED85.3, LED86.4
unnamed: LED86.2, LED87.5
unnamed: LED86.3, LED87.4
unnamed: LED87.2, LED88.5
unnamed: LED87.3, LED88.4
unnamed: LED88.2, LED89.5
unnamed: LED88.3, LED89.4
unnamed: LED89.2, LED90.5
unnamed: LED89.3, LED90.4
unnamed: LED90.2, LED91.5
unnamed: LED90.3, LED91.4
unnamed: LED91.2, LED92.5
unnamed: LED91.3, LED92.4
unnamed: LED92.2, LED93.5
unnamed: LED92.3, LED93.4
unnamed: LED93.2, LED94.5
unnamed: LED93.3, LED94.4
unnamed: LED94.2, LED95.5
unnamed: LED94.3, LED95.4
unnamed: LED95.2, LED96.5
unnamed: LED95.3, LED96.4
unnamed: LED96.2, LED97.5
unnamed: LED96.3, LED97.4
unnamed: LED97.2, LED98.5
unnamed: LED97.3, LED98.4
unnamed: LED98.2, LED99.5
unnamed: LED98.3, LED99.4
unnamed: LED100.2, LED101.5
unnamed: LED100.3, LED101.4
unnamed: LED99.3, LED100.4
unnamed: LED99.2, LED100.5
unnamed: LED101.2, LED102.5
unnamed: LED101.3, LED102.4
unnamed: LED102.2, LED103.5
unnamed: LED102.3, LED103.4
unnamed: LED103.2, LED104.5
unnamed: LED103.3, LED104.4
unnamed: LED105.2, LED106.5
unnamed: LED105.3, LED106.4
unnamed: LED106.2, LED107.5
unnamed: LED106.3, LED107.4
unnamed: LED107.2, LED108.5
unnamed: LED107.3, LED108.4
unnamed: LED108.2, LED109.5
unnamed: LED108.3, LED109.4
unnamed: LED109.2, LED110.5
unnamed: LED109.3, LED110.4
unnamed: LED110.2, LED111.5
unnamed: LED110.3, LED111.4
unnamed: LED111.2, LED112.5
unnamed: LED111.3, LED112.4
unnamed: LED112.2, LED113.5
unnamed: LED112.3, LED113.4
unnamed: LED113.2, LED114.5
unnamed: LED113.3, LED114.4
unnamed: LED114.2, LED115.5
unnamed: LED114.3, LED115.4
unnamed: LED115.2, LED116.5
unnamed: LED115.3, LED116.4
unnamed: LED116.2, LED117.5
unnamed: LED116.3, LED117.4
unnamed: LED117.2, LED118.5
unnamed: LED117.3, LED118.4
unnamed: LED118.2, LED119.5
unnamed: LED118.3, LED119.4
unnamed: LED119.2, LED120.5
unnamed: LED119.3, LED120.4
unnamed: LED120.2, LED121.5
unnamed: LED120.3, LED121.4
unnamed: LED121.2, LED122.5
unnamed: LED121.3, LED122.4
unnamed: LED122.2, LED123.5
unnamed: LED122.3, LED123.4
unnamed: LED123.2, LED124.5
unnamed: LED123.3, LED124.4
unnamed: LED124.2, LED125.5
unnamed: LED124.3, LED125.4
unnamed: LED125.2, LED126.5
unnamed: LED125.3, LED126.4
unnamed: LED126.2, LED127.5
unnamed: LED126.3, LED127.4
unnamed: LED127.2, LED128.5
unnamed: LED127.3, LED128.4
unnamed: LED129.2, LED130.5
unnamed: LED129.3, LED130.4
unnamed: LED130.2, LED131.5
unnamed: LED130.3, LED131.4
unnamed: LED131.2, LED132.5
unnamed: LED131.3, LED132.4
unnamed: LED132.2, LED133.5
unnamed: LED132.3, LED133.4
unnamed: LED133.2, LED134.5
unnamed: LED133.3, LED134.4
unnamed: LED134.2, LED135.5
unnamed: LED134.3, LED135.4
unnamed: LED135.2, LED136.5
unnamed: LED135.3, LED136.4
unnamed: LED136.2, LED137.5
unnamed: LED136.3, LED137.4
unnamed: LED137.2, LED138.5
unnamed: LED137.3, LED138.4
unnamed: LED138.2, LED139.5
unnamed: LED138.3, LED139.4
unnamed: LED139.2, LED140.5
unnamed: LED139.3, LED140.4
unnamed: LED140.2, LED141.5
unnamed: LED140.3, LED141.4
unnamed: LED141.2, LED142.5
unnamed: LED141.3, LED142.4
unnamed: LED142.2, LED143.5
unnamed: LED142.3, LED143.4
unnamed: LED143.2, LED144.5
unnamed: LED143.3, LED144.4
unnamed: LED144.2, LED145.5
unnamed: LED144.3, LED145.4
unnamed: LED145.2, LED146.5
unnamed: LED145.3, LED146.4
unnamed: LED146.2, LED147.5
unnamed: LED146.3, LED147.4
unnamed: LED147.2, LED148.5
unnamed: LED147.3, LED148.4
unnamed: LED148.2, LED149.5
unnamed: LED148.3, LED149.4
unnamed: LED149.2, LED150.5
unnamed: LED149.3, LED150.4
unnamed: LED150.2, LED151.5
unnamed: LED150.3, LED151.4
unnamed: LED151.2, LED152.5
unnamed: LED151.3, LED152.4
unnamed: LED153.2, LED154.5
unnamed: LED153.3, LED154.4
unnamed: LED154.2, LED155.5
unnamed: LED154.3, LED155.4
unnamed: LED155.2, LED156.5
unnamed: LED155.3, LED156.4
unnamed: LED156.2, LED157.5
unnamed: LED156.3, LED157.4
unnamed: LED157.2, LED158.5
unnamed: LED157.3, LED158.4
unnamed: LED158.2, LED159.5
unnamed: LED158.3, LED159.4
unnamed: LED159.2, LED160.5
unnamed: LED159.3, LED160.4
unnamed: LED160.2, LED161.5
unnamed: LED160.3, LED161.4
unnamed: LED161.2, LED162.5
unnamed: LED161.3, LED162.4
unnamed: LED162.2, LED163.5
unnamed: LED162.3, LED163.4
unnamed: LED163.2, LED164.5
unnamed: LED163.3, LED164.4
unnamed: LED164.2, LED165.5
unnamed: LED164.3, LED165.4
unnamed: LED165.2, LED166.5
unnamed: LED165.3, LED166.4
unnamed: LED166.2, LED167.5
unnamed: LED166.3, LED167.4
unnamed: LED167.2, LED168.5
unnamed: LED167.3, LED168.4
unnamed: LED168.2, LED169.5
unnamed: LED168.3, LED169.4
unnamed: LED169.2, LED170.5
unnamed: LED169.3, LED170.4
unnamed: LED170.2, LED171.5
unnamed: LED170.3, LED171.4
unnamed: LED171.2, LED172.5
unnamed: LED171.3, LED172.4
RESET: J1.3, SW1.1, U2.26
SWCLK: J1.4, R4.2, U2.31
SWDIO: J1.2, U2.32
USB_D+: J2.3, U2.24
USB_D-: J2.2, U2.23

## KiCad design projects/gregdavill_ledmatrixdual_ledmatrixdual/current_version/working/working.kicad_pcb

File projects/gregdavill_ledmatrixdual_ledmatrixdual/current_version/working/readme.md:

# ledmatrixdual
 
## summary 
* id: gregdavill_ledmatrixdual_ledmatrixdual
* user: gregdavill
* name: ledmatrixdual
* board: ledmatrixdual
* repo: https://github.com/gregdavill/ledMatrixDual
* src_file_repo_kicad_pcb: ledMatrixDual.kicad_pcb
* src_file_repo_kicad_pcb_link: https://github.com/gregdavill/ledMatrixDual/tree/master/ledMatrixDual.kicad_pcb

* src_file_repo_sch: ledMatrixController/ledMatrixDual.sch
* src_file_repo_sch_link: https://github.com/gregdavill/ledMatrixDual/tree/master/ledMatrixController/ledMatrixDual.sch
* full details link: https://github.com/oomlout/oomlout_oomp_project_bot_v_2/tree/main/projects/gregdavill_ledmatrixdual_ledmatrixdual/current_version/working

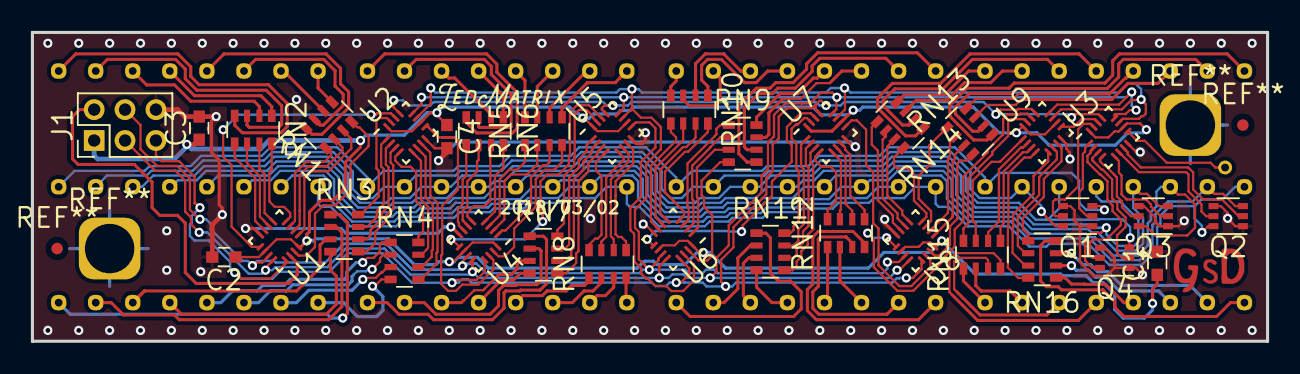
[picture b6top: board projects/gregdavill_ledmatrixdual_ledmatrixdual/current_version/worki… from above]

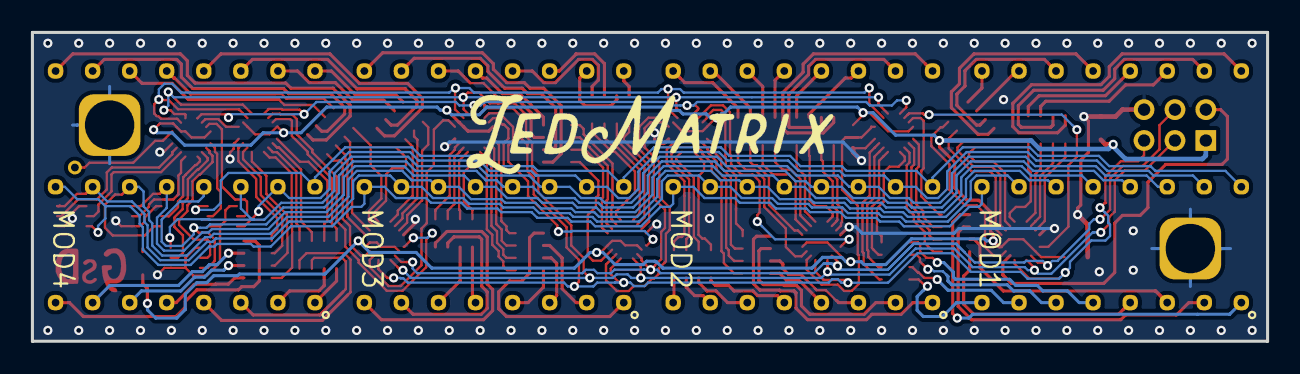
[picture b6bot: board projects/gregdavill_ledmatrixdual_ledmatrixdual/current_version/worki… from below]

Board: 2 copper layers, 80.0 x 20.0 mm, 38 parts (4 on the bottom side), 158 nets.

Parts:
C1, C2, C3, C4: 100n; C_0603
J1: Conn_02x03_Odd_Even; Pin_Header_Straight_2x03_Pitch2.00mm
MOD1, MOD2, MOD3, MOD4: KEM-7088
Q1, Q2, Q3, Q4: DMN53D0LDW; SOT-363_SC-70-6
RN1, RN2, RN3, RN4, RN5, RN6, RN7, RN8, RN9, RN10, RN11, RN12, RN13, RN14, RN15, RN16: R_Pack04; R_Array_Convex_4x0603
U1, U2, U3, U4, U5, U6, U7, U8, U9: SN74HC595B; UQFN-16-1EP_3x3mm_Pitch0.5mm

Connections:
+3V3: C1.1, C2.1, C3.1, C4.1, J1.1, U1.10, U1.16, U2.10, U2.16, U3.10, U3.16, U4.10, U4.16, U5.10, U5.16, U6.10, U6.16, U7.10, U7.16, U8.10, U8.16, U9.10, U9.16
/ledCommon/SIN: U3.14, U9.9
/ledModule_1/SIN: U2.9, U4.14
/ledModule_2/SIN: U5.9, U6.14
/ledModule_3/SIN: U7.9, U8.14
CLK: J1.4, U1.11, U2.11, U3.11, U4.11, U5.11, U6.11, U7.11, U8.11, U9.11
GND: C1.2, C2.2, C3.2, C4.2, J1.6, Q1.1, Q1.4, Q2.1, Q2.4, Q3.1, Q3.4, Q4.1, Q4.4, U1.8, U2.8, U3.8, U4.8, U5.8, U6.8, U7.8, U8.8, U9.8
LED_COM0: MOD1.16, MOD2.16, MOD3.16, MOD4.16, Q2.6
LED_COM1: MOD1.15, MOD2.15, MOD3.15, MOD4.15, Q2.3
LED_COM2: MOD1.14, MOD2.14, MOD3.14, MOD4.14, Q3.6
LED_COM3: MOD1.13, MOD2.13, MOD3.13, MOD4.13, Q3.3
LED_COM4: MOD1.12, MOD2.12, MOD3.12, MOD4.12, Q4.6
LED_COM5: MOD1.11, MOD2.11, MOD3.11, MOD4.11, Q4.3
LED_COM6: MOD1.10, MOD2.10, MOD3.10, MOD4.10, Q1.6
LED_COM7: MOD1.9, MOD2.9, MOD3.9, MOD4.9, Q1.3
unnamed: MOD1.1, RN3.1
unnamed: MOD1.2, RN3.2
unnamed: MOD1.3, RN3.3
unnamed: MOD1.4, RN3.4
unnamed: MOD1.5, RN4.1
unnamed: MOD1.6, RN4.2
unnamed: MOD1.7, RN4.3
unnamed: MOD1.8, RN4.4
unnamed: MOD1.17, RN2.4
unnamed: MOD1.18, RN2.3
unnamed: MOD1.19, RN2.2
unnamed: MOD1.20, RN2.1
unnamed: MOD1.21, RN1.8
unnamed: MOD1.22, RN1.7
unnamed: MOD1.23, RN1.6
unnamed: MOD1.24, RN1.5
unnamed: MOD2.1, RN7.1
unnamed: MOD2.2, RN7.2
unnamed: MOD2.3, RN7.3
unnamed: MOD2.4, RN7.4
unnamed: MOD2.5, RN8.1
unnamed: MOD2.6, RN8.2
unnamed: MOD2.7, RN8.3
unnamed: MOD2.8, RN8.4
unnamed: MOD2.17, RN6.4
unnamed: MOD2.18, RN6.3
unnamed: MOD2.19, RN6.2
unnamed: MOD2.20, RN6.1
unnamed: MOD2.21, RN5.8
unnamed: MOD2.22, RN5.7
unnamed: MOD2.23, RN5.6
unnamed: MOD2.24, RN5.5
unnamed: MOD3.1, RN11.1
unnamed: MOD3.2, RN11.2
unnamed: MOD3.3, RN11.3
unnamed: MOD3.4, RN11.4
unnamed: MOD3.5, RN12.1
unnamed: MOD3.6, RN12.2
unnamed: MOD3.7, RN12.3
unnamed: MOD3.8, RN12.4
unnamed: MOD3.17, RN10.4
unnamed: MOD3.18, RN10.3
unnamed: MOD3.19, RN10.2
unnamed: MOD3.20, RN10.1
unnamed: MOD3.21, RN9.8
unnamed: MOD3.22, RN9.7
unnamed: MOD3.23, RN9.6
unnamed: MOD3.24, RN9.5
unnamed: MOD4.1, RN15.1
unnamed: MOD4.2, RN15.2
unnamed: MOD4.3, RN15.3
unnamed: MOD4.4, RN15.4
unnamed: MOD4.5, RN16.1
unnamed: MOD4.6, RN16.2
unnamed: MOD4.7, RN16.3
unnamed: MOD4.8, RN16.4
unnamed: MOD4.17, RN14.4
unnamed: MOD4.18, RN14.3
unnamed: MOD4.19, RN14.2
unnamed: MOD4.20, RN14.1
unnamed: MOD4.21, RN13.8
unnamed: MOD4.22, RN13.7
unnamed: MOD4.23, RN13.6
unnamed: MOD4.24, RN13.5
unnamed: Q1.2, U3.1
unnamed: Q1.5, U3.15
unnamed: Q2.2, U3.7
unnamed: Q2.5, U3.6
unnamed: Q3.2, U3.5
unnamed: Q3.5, U3.4
unnamed: Q4.2, U3.3
unnamed: Q4.5, U3.2
unnamed: RN1.1, U1.3
unnamed: RN1.2, U1.2
unnamed: RN1.3, U1.1
unnamed: RN1.4, U1.15
unnamed: RN2.5, U1.7
unnamed: RN2.6, U1.6
unnamed: RN2.7, U1.5
unnamed: RN2.8, U1.4
unnamed: RN3.5, U2.3
unnamed: RN3.6, U2.2
unnamed: RN3.7, U2.1
unnamed: RN3.8, U2.15
unnamed: RN4.5, U2.7
unnamed: RN4.6, U2.6
unnamed: RN4.7, U2.5
unnamed: RN4.8, U2.4
unnamed: RN5.1, U4.3
unnamed: RN5.2, U4.2
unnamed: RN5.3, U4.1
unnamed: RN5.4, U4.15
unnamed: RN6.5, U4.7
unnamed: RN6.6, U4.6
unnamed: RN6.7, U4.5
unnamed: RN6.8, U4.4
unnamed: RN7.5, U5.3
unnamed: RN7.6, U5.2
unnamed: RN7.7, U5.1
unnamed: RN7.8, U5.15
unnamed: RN8.5, U5.7
unnamed: RN8.6, U5.6
unnamed: RN8.7, U5.5
unnamed: RN8.8, U5.4
unnamed: RN9.1, U6.3
unnamed: RN9.2, U6.2
unnamed: RN9.3, U6.1
unnamed: RN9.4, U6.15
unnamed: RN10.5, U6.7
unnamed: RN10.6, U6.6
unnamed: RN10.7, U6.5
unnamed: RN10.8, U6.4
unnamed: RN11.5, U7.3
unnamed: RN11.6, U7.2
unnamed: RN11.7, U7.1
unnamed: RN11.8, U7.15
unnamed: RN12.5, U7.7
unnamed: RN12.6, U7.6
unnamed: RN12.7, U7.5
unnamed: RN12.8, U7.4
unnamed: RN13.1, U8.3
unnamed: RN13.2, U8.2
unnamed: RN13.3, U8.1
unnamed: RN13.4, U8.15
unnamed: RN14.5, U8.7
unnamed: RN14.6, U8.6
unnamed: RN14.7, U8.5
unnamed: RN14.8, U8.4
unnamed: RN15.5, U9.3
unnamed: RN15.6, U9.2
unnamed: RN15.7, U9.1
unnamed: RN15.8, U9.15
unnamed: RN16.5, U9.7
unnamed: RN16.6, U9.6
unnamed: RN16.7, U9.5
unnamed: RN16.8, U9.4
unnamed: U1.9, U2.14
unnamed: U4.9, U5.14
unnamed: U6.9, U7.14
unnamed: U8.9, U9.14
OE: J1.5, U1.13, U2.13, U3.13, U4.13, U5.13, U6.13, U7.13, U8.13, U9.13
RCLK: J1.3, U1.12, U2.12, U3.12, U4.12, U5.12, U6.12, U7.12, U8.12, U9.12
SER: J1.2, U1.14
